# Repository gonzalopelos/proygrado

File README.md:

# Proyecto RAS
Repositorio para versionado de componentes del proyecto RAS
## Configuracion del ambiente de desarrollo
Tenemos dos entornos de desarrollo, uno para desarrollar el firmware de la placa __FDRM-K64__ y otro para desarrollar una aplicacion cliente de consola.
### Entorno de desarrollo para el firmware
* IDE: [Kinetis® Design Studio Integrated Development Environment] (http://www.nxp.com/products/software-and-tools/run-time-software/kinetis-software-and-tools/ides-for-kinetis-mcus/kinetis-design-studio-integrated-development-environment-ide:KDS_IDE#).

### Entorno de desarrollo para la aplicacion cliente de consola
* IDE: [CLion] (https://www.jetbrains.com/clion/download/#section=linux-version).

Para instalarlo seguir los siguientes pasos:

1. Descargarlo desde el link anterior
2. Modificar la fecha de la pc estableciendola algunos anos en el futuro
3. Instalar el IDE
4. Ejecutar el IDE indicando que se desea utilizar la Trial Version
5. Cerrar el IDE.
6. Volver a establecer la fecha de la pc correctamente.
8. Listo, la trial durara hasta que la gente de JetBrains se avive o hasta que se cumpla la fecha establecida  30 dias.

## Deploy del Firmware
Una vez compilado el firmware base simplemente se debe conectar la placa y copiar el archivo __ras_fdrm.bin__ generado en la compilacion al directorio (usb storage) de la placa. Una vez que la placa lo detecta se instala automaticamente, solo resta presionar el boto Reset de dicha placa y se comenzara a ejecutar la rutina del firmware.

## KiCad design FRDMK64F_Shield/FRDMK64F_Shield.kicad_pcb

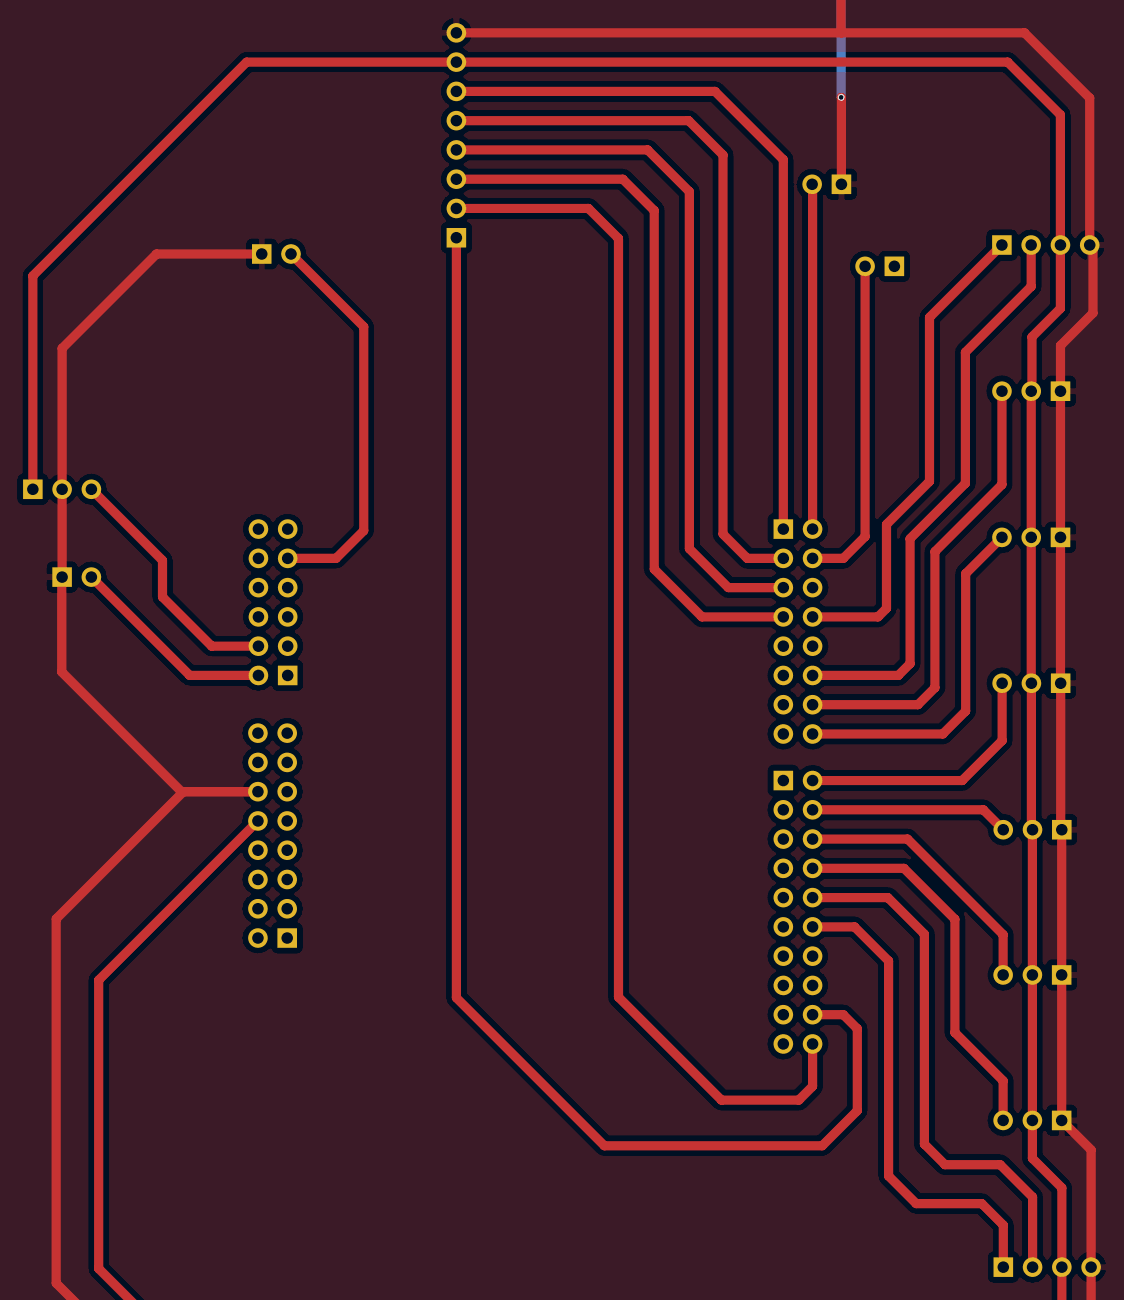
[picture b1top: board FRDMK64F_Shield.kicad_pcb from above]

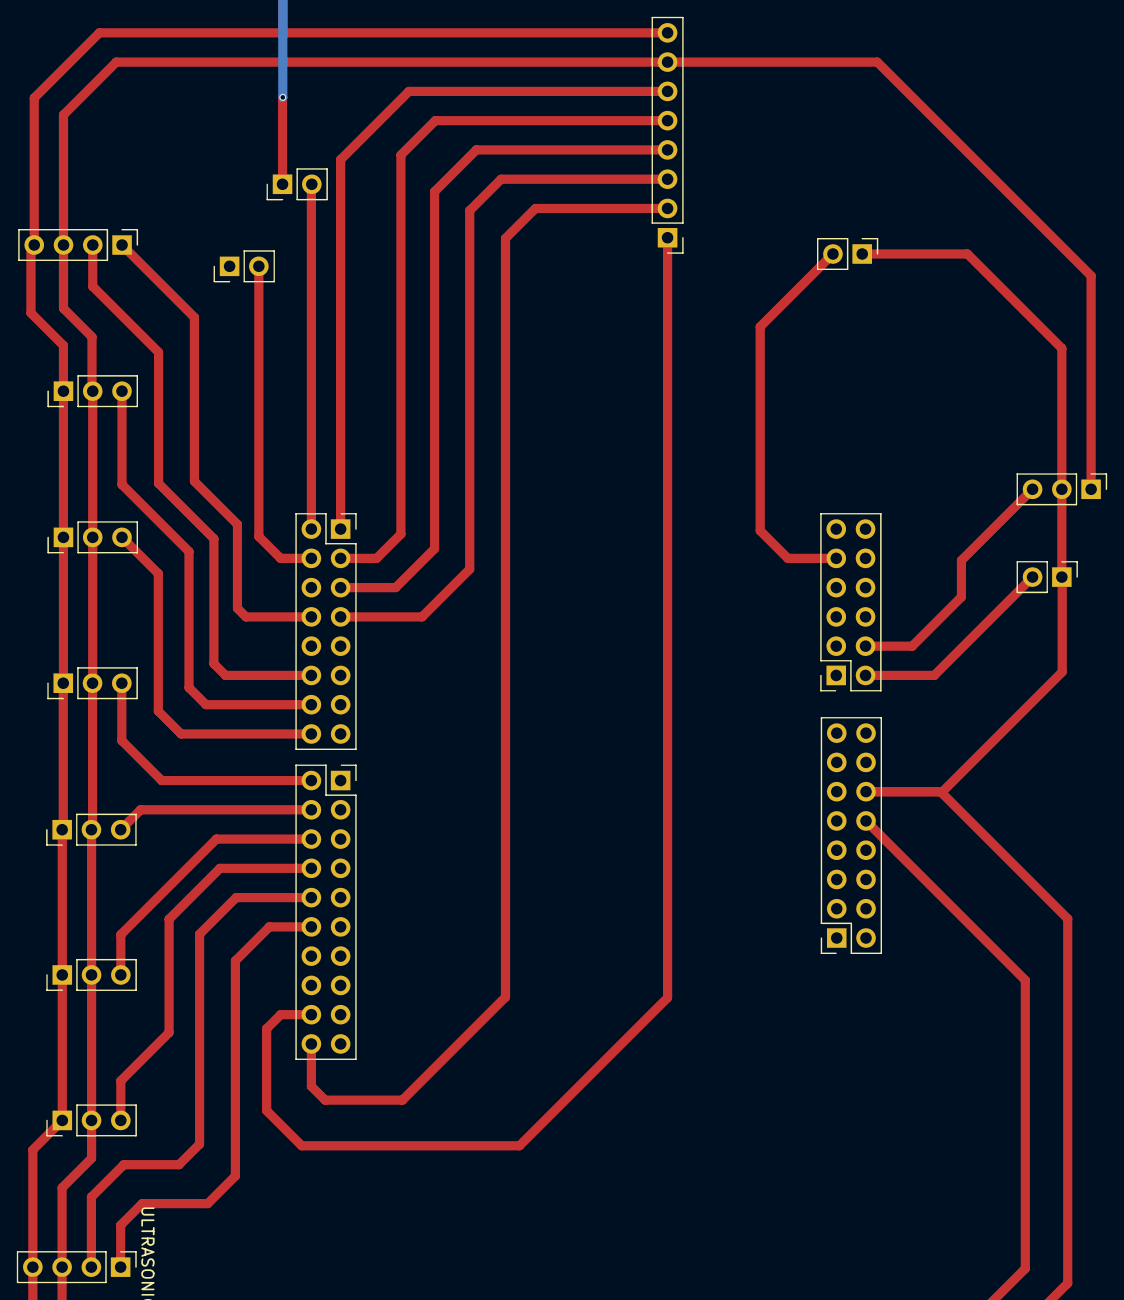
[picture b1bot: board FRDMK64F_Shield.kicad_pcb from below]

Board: 2 copper layers, 18 parts (18 on the bottom side), 23 nets.

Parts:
BATTERY1: CONN_01X03; Pin_Header_Straight_1x03_Pitch2.54mm
BREAK1: CONN_01X02; Pin_Header_Straight_1x02_Pitch2.54mm
CINTA1: CONN_01X8; Pin_Header_Straight_1x08_Pitch2.54mm
ENABLED1: CONN_01X02; Pin_Header_Straight_1x02_Pitch2.54mm
HALL_0, HALL_1, HALL_2, HALL_3, HALL_4, HALL_5: CONN_01X03; Pin_Header_Straight_1x03_Pitch2.54mm
HORN1: CONN_01X02; Pin_Header_Straight_1x02_Pitch2.54mm
J1, J3: CONN_02X08; Socket_Strip_Straight_2x08_Pitch2.54mm
J2: CONN_02X10; Socket_Strip_Straight_2x10_Pitch2.54mm
J4: CONN_02X06; Socket_Strip_Straight_2x06_Pitch2.54mm
POWER1: CONN_01X02; Pin_Header_Straight_1x02_Pitch2.54mm
ULTRASONIC_1, ULTRASONIC_2: CONN_01X04; Pin_Header_Straight_1x04_Pitch2.54mm

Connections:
/BATTERY: BATTERY1.3, J4.4
/BREAK: BREAK1.2, J1.4
/GND: BATTERY1.2, CINTA1.8, ENABLED1.1, HALL_0.1, HALL_1.1, HALL_2.1, HALL_3.1, HALL_4.1, HALL_5.1, HORN1.1, J3.12, POWER1.1, ULTRASONIC_1.4, ULTRASONIC_2.4
/HALL0_INT: HALL_0.3, J2.8
/HALL1_INT: HALL_1.3, J2.6
/HALL2_INT: HALL_2.3, J2.4
/HALL3_INT: HALL_3.3, J2.2
/HALL4_INT: HALL_4.3, J1.16
/HALL5_INT: HALL_5.3, J1.14
/HORN: HORN1.2, J4.9
/I2C_SCL: CINTA1.2, J2.20
/I2C_SDA: CINTA1.1, J2.18
/P5V_USB: BATTERY1.1, CINTA1.7, HALL_0.2, HALL_1.2, HALL_2.2, HALL_3.2, HALL_4.2, HALL_5.2, J3.10, ULTRASONIC_1.3, ULTRASONIC_2.3
/POWER: J4.2, POWER1.2
/REV_M0: CINTA1.3, J1.7
/REV_M1: CINTA1.4, J1.5
/REV_M2: CINTA1.5, J1.3
/REV_M3: CINTA1.6, J1.1
/ULTRA1_ECHO: J1.12, ULTRASONIC_1.2
/ULTRA1_TRIG: J1.8, ULTRASONIC_1.1
/ULTRA2_ECHO: J2.10, ULTRASONIC_2.2
/ULTRA2_TRIG: J2.12, ULTRASONIC_2.1
unnamed: ENABLED1.2, J1.2

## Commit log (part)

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2015-08-17 Firmware and custom demos
    Código del firmware y demos para interactuar con la placa. PIC18F45K50.
2015-08-20 se eliminan archivos que no deben estar versionados y se agerga configuración al gitignore.
2015-08-22 Tuti!
2015-09-16 Modificaciones realizadas para leer un boton y variar la frecuencia de parpadeo de un led
2015-10-09 Codigo para leer una entrada analogica en el pin RA3 y generar una salida digital en el pin RB2. Acceder a los links presentes en el metodo init para entender las configuraciones
2015-10-16 Se agerga POC en la que se utiliza HIDAPI para ejecutar comandos desde una aplicacion de consola hecha en C
2015-10-17 HID Test para Windows
2015-10-28 Se agrega operacion 0x9C al firmware para leer desde el bufer USB y escribir los caracteres leidos con un shift, si leo 0 escribo 1.
2015-10-28 Se incorpora el comando 100 al host de test para enviar cuatro ceros a la placa y espera leer lo que responde la placa (cuatro unos)
2015-10-28 Se agregan las operacines 101 y 102 al host para escribir y leer respectivamente, de esa forma se pudo probar que no es posible establecer dos conexiones con dos host a la placa y leer con uno lo que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
2016-05-14 Hdlc_Poc: Verson inicial.
2016-05-25 Modificaciones que incluyen la implementacion de yahdlc en el Firmware. NOTA IMPORTANTE: el metodo ProcessIo esta retornando la misma data que lee sin importar el comando que recibe y ademas esta eje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
2016-07-16 Se eliminan archivos obsoletos.
2016-07-21 Se agrega aplicacion SBC de consola, cliente para comunicarse con la placa. Esta aplicacion puede compilarse y ejecutarse como un poryecto CMake con CLion.
2016-07-23 Se agrega firmware base previo a editarlo con Kinetis Studio.
2016-08-31 Modificaciones para desarrollo de un controlador HDLC.
2016-08-31 HDLC :: Diagrama de estados en PlantText.
2016-09-03 Diagramas de estados para el Emisor y Receptor de HDLC.
2016-09-10 Avances en el desarrollo de HDLC.
2016-09-10 Avances en la imlementacion de HDCL.
2016-09-11 Versión inicial de una implementación básica del protocolo HDLC.
2016-09-18 Implementation de HDLC. + Se extiende yahdlc para considerar direcciones de estaciones. + Se incorpora uso de semáforos para establecer la conexión emisor-receptor en ambas estaciones. + Se agregan o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
2016-09-21 Modificaciones sobre HDLC. + Se agrega manejo de time_out en la espera de ACKs + Correcciones de errores en general.
2016-09-24 Subo proyecto nuevo para pruebas de i2c con el acelerómetro y magnetómetro. También agrego librería para manejo de acelerómetro en ras_frdm pero no funciona.
2016-09-28 se eliminan archivos que deben estar ignorados.
2016-09-28 Programa de test para el DAC PCF8591 incluido en la placa de demo YL-40. El programa incrementa de a 1 cada un segundo un valor que es escrito en el DAC para que sea su salida analogica. El resultado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
2016-09-29 Agrego ras_frdm con el ejemplo para el DAC descargado de mbed para kds 3. Agrego archivos faltantes para el ejemplo del acelerómetro y magnetómetro.
2016-09-29 Agrego archivos faltantes a la carpeta TOOLCHAIN_GCC_ARM
2016-09-30 Se incorpora el manejo de Threads en la implementación de HDLC.
2016-10-11 Modificaciones para establecer la conexión HDLC.
2016-10-29 Se movieron las librerias bajo la carpeta modules
2016-10-29 que lio
2016-11-05 Se incluyen librerias DM3Module, EmBencode y MCC
2016-11-12 un commit ahi
2016-11-15 Se borra archivo innecesario.
2016-11-18 + Se agrega librería EthernetInterface para implementación de consola para Debug. + Se actualizan las librerías mbed_rtos y mbed.
2016-11-23 Se divide el main en 2 secciones considerando la definicion de MAIN_AM. Si esta definida se ejecuta el main de Alberto Martinucci, si no se ejecuta el main de Gonzalo Pelos
2016-11-23 Archivos faltantes para hacer commit completo
2016-12-18 Se modifican definiciones de macros para redefinir en la librería Ethernet las que ya estaban definidas en errno.h
2016-12-18 Modificaciones en Logger para registrar un mensaje ALIVE cuando no hay nada para logear.
2016-12-18 [OBSOLETO] Se deja definida la variable del compilador MAIN_AM para excluir lógica particular para OSX a la hora de resolver la comunicación serial con la placa desde la aplicación cliente SBC.
2016-12-18 Se incorpora el comando 7 que envía datos a la placa mediante TCP y deja impreso la cantidad de bytes enviados/recibidos en el tiempo que haya tomado.
2017-01-21 + Update EmBencode implementation to commit [577d8d3ea8e0ba634d357a1a3aeb9a36a4bde524] (https://gitlab.fing.edu.uy/dm3/firmware/commit/577d8d3ea8e0ba634d357a1a3aeb9a36a4bde524). + Add module MCC with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
2017-01-28 + Add MCC states diagram + Progress in implementing the MCC module.
2017-02-09 + Fix dependencies of Mcc on runtime
2017-02-23 MCC :: Fixes.
2017-02-28 + EmBencode Refactor
2017-03-01 Borro porquerias
2017-03-01 Cambio uso de bcopy/bzero por memcpy/memset para copiar/limpiar memoria. Los metodos anteriores no son portables y estan deprecated.
2017-03-01 + refactor namespaces
2017-03-05 + Add lyx docs.
2017-03-11 Subo modificaciones basicas en el archivo LyX de estado del arte. Comiteo que se ignore el archivo pdf generado por LyX, el archivo de backup del lyx y el archivo de backup de las referencias.
2017-03-14 Se agregan referencias al archivo de bibliografia. Se agregan autores al estado del arte. Se modifica estilo de la bibliografia en el estado del arte. Se agrega seccion 3 (Seguridad en Robots Colabor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
2017-03-14 Se agregan mas referencias. Se paso del estado del arte del drive hasta la seccion 3 completa. Se agrega un archivo LaTeX para ser incluido en el estado del arte como pagina de inicial
2017-03-23 Add ROS node for TCP communication
    Version de prueba con servicios dummies.
2017-03-25 Se agrega MotorModule al proyecto.
2017-03-30 SBC/main: Se agrega comando nro 4 que envia via mcc la solicitud de ejecucion de la funcion de test de los motores.
    ras_frdm/main
    Se crea el modulo motor
    ras_frdm/modules/Motor/MotorModule.cpp y MotorModule.h
    Se cambia definicion de variable de error i2c, daba error de ya definida previamente de la forma en que estaba.
2017-04-06 ROS tcp_comm + Se agrega procesamiento de mensajes desde la ioboard + Se agerga publisher para mensajes que llegan desde la ioboard + Se agrega procesamiento de mensajes que llegan de nodos ros para 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
2017-04-16 ROS - tcp_comm
    + Se implementa el procesamiento de mensajes desde la ioboard y se publican en el topic /dm3/mcc2pc
    + Correcciones asociadas a la lectura bloqueante del socket
2017-04-16 modifico .gitignore para incoroporar carpeta con archivos necesarios para el debug con el IDE roboware.
2017-05-02 Se agregan todas las placas y conclusiones de las mismas al documento de estado del arte.
2017-05-03 Se agregan referencias faltantes.
2017-05-06 Fix IP Address hardcoded in Tcp_Controller.cpp
2017-05-09 Revert "main con test del ultrasonido"
    This reverts commit b0374bd0593d25aeddc2238457377dc51b75ac24.
2017-05-09 Commit teta
2017-05-21 commit de mi main de pruebas
2017-05-21 resuelvo conflictos entre main AM y main GP
2017-05-23 Nueva clase Bumper, main y cproject con includes nuevos.
2017-05-30 Creo un grupo de imagenes y lo aplico a todas las del documento para que ocupen el 50% del ancho de la pagina.
2017-06-06 resolve conflicts after pull command.
2017-06-10 + add utility function to invoke callbacks in self-mode
2017-06-13 + Add linked_list type to utilities folder + Refactor Dm3Module & Dm3Security to handle and reports alerts
2017-06-22 Add diagram
    SBC and IO Board clases
2017-06-27 + Dm3Security logic to check TCP connection + implement Singleton pattern in Admin module
2017-06-30 Includes fix
    Fix the case on modules to be included (MCC and DM3) in Admin.h and MotorModule.h.
2017-07-04 + Add DM3 states diagram
2017-07-05 + modify DM3_States diagram.
2017-07-23 Fix memory leak.
2017-07-25 +add logger for ROS +set non blocking connect to sockets
2017-07-25 Quito clases del modulos relacionados con el puerto K64F USB. Se agrega al main codigo de ejemplo de deteccion de la fuente de reset, en particular para detectar un reset por WATCHDOG TIMEOUT
2017-07-27 Watchdog fixed.
    New: constructor method that unlocks, sets timeout, enables and kicks watchdog.
    New: timeout as a class member variable.
    New: public method getTimeoutValue that resturns the watchdog's timeout value expressed in seconds.
    New: private method reportResetStatus that sends to the USB Open SDA interface the source of the last reset (POWER ON, EXTERNAL PIN, WATCHDOG, OTHER).
    Edit: on kick mehtod interrupts must be disabled prior to the mehtod's logic execution, interrupts are re-enabled after execution of watchdog refresh sentences.
    Note: Watchdog object must be constructed right after reset otherwise undesired watchdog resets may occur.
2017-07-28 Bumper class --> Edit: Modified to detect both ascendant and descendant flanks when the bumper is pressed/released. Edit: Default bumper debouncig timeout set to 100ms
    DM3Security class -->
    Edit: Modified to swich between DANGER and OK states when the bumper is pressed/released.
2017-07-28 Comment printf function in modules.
2017-07-28 resolve pull-rebase conflicts.
2017-07-28 Dm3Module class --> Edit: Add bumper state alert method. Edit: Attach bumper state alert method to security instance.
    Dm3Security class -->
    Edit: Callback typedef, add alert event for bumper umpressed.
    Edit: attach method, add attach callback to bumper umpressed alert.
2017-07-28 Watchdog class --> Add: resetStatus class memeber. Edit: constructor, remove print to debug port of reset source. Set value of class member resetStatus with the source of last reset. Add: getLastRese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
    Dm3Moule class -->
    Add: Watchdog as extern variable.
    Add: report_last_reset_source to send a report regarding the source of the last reset. The report includes de reset source code and a reset source description.
    Add: OPCODE_RESET = 4, new opcode for the handler of the reset source report.
    Edit: DM3_OPCODES set to 4.
    main -->
2017-08-01 Fix create threads error.
2017-08-09 disable mcc messages by serial connection.
2017-08-10 Reporte de status simple
    Solo reporta status general
2017-08-11 + fixes in update sd status + fixes in speed checks + print mcc (serial) for security module + send complete mcc message in security reports
2017-08-14 + cambio velocidad máxima permitida + corrijo pid reportado para mcc de reporte de seguridad.
2017-08-18 + agrego chequeo de sobre carga de potencia en los motores. Le falta reportar y tomar acciones.
2017-08-30 Add kicad project for k64F shield.
2017-09-01 Avances en el pcb
2017-09-01 Primera versión del PCB completo.
2017-09-04 Modificaciones en PCB.
2017-09-08 Se agrega speed check
    Se vuelve a agregar
2017-09-10 Agrego alerta de inconsistencia entre la variación de potencia y velocidad.
2017-09-18 +fixes +traza para depuración
2017-09-20 + fixes en el handle reverse + se borra código innecesario en tcpsocketconnection
2017-10-04 modificaciones para restablecer conexión tcp.
2017-10-16 + Fixes on setting angular speeds.
2017-10-19 Fix to handle reverse Fix to speeds checks
2017-10-24 Security Report on Status Change
    Sólo se envían reportes de estado cuando existe un cambio de estado en un dispositivo.
2017-10-24 + Set 1 m to minimum allowed distance in ultrasonic device. + Fix reverse
2017-10-30 + renombro diagramas para agregar la extensión .wsd (Plugin vs code PlantUML). + avanzo en el diagrama de componentes del firmware
2017-11-01 Se incorpora mecanismo de seguridad para controlar comunicación i2c con motores.
2017-11-01 Fix i2c motors status checks
2017-11-16 desarrollo de diagramas para la documentación.
2017-11-20 Diagramas e imágenes del PCB y esquemático.
2017-11-23 modificación de diagramas.
2017-11-27 Agrego el informe latex al repo.
2017-11-28 Se agregan imagenes del shield + correcciones generales
2017-11-29 Se agregan recuperación frente a fallas y bibliografía
2017-11-29 Completo requerimientos
2017-11-30 Se agregan referencia y correciones menores en técnicas de seguridad.
2017-11-30 Guíá - Técnicas
    Se completa la sección, se agregan referencias.
2017-12-01 elimino comentarios en sección evaluación de resultados.
2017-12-01 Trabajos a futuro
    Nuevo prototipo con diseño seguro (se puede mejorar)
2017-12-02 Se reestructura y desarrolla Trabajos a futuro
2017-12-02 documentación asociada a la plataforma utilizada.
2017-12-03 Se agregan más texto a conclusiones
2017-12-03 modifcaciones en las conclusiones.
2017-12-03 Se desarrolla conclusión de la discordia
2017-12-03 Correccion minima en conclusion de la discordia
2017-12-03 Corrección
2017-12-03 Correcciones en readacción y otros
2017-12-03 revisión gral y correcciones.
2017-12-04 Correcciones generales
2017-12-04 Correciones generales
